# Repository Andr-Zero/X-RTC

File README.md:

# X-RTC
A supplemental Real Time Clock for the Original Xbox 

The Original Xbox does not keep time when unplugged for an extended period of time. While some homebew apps have NTP functionality built in, not everyone plugs the console into their home network every time they play. 

Designed so the battery is only used when AC power is removed from the console. A CR2032 in theory should last 6-10 years when constantly being used. 
Should work with any modchip and TSOPed consoles. Have not tested with BFM BIOSes. 

SDA\SDL from the console are also brought to a set of solder pads for ease of installation of any other mod that may require them. 

# Board Specifications
0.8mm thick, castellated holes on all sides.

# 1.0-1.4 Installation
On the bottom of the Xbox motherboard. If you have a pinheader already installed, remove excessive solder from the pins outlined in purple and any that would interfere with the installation of the X-RTC QSB. Install the QSB onto the LPC port as shown above, make sure the QSB is sitting flush against the board. While keeping the QSB aligned, solder the QSB to the LPC port and the ground point outlined in black. Run a short wire from the console's 3.3v standby outlined in red to the 3v3 StdBy pad on the QSB. Lastly wire a 3v battery to the Positive and Negative solder pads on the QSB.

# 1.6 Installation
On the bottom of the Xbox motherboard. Remove any existing LPC rebuild QSB or wires that maybe installed. If a pinheader is already installed, remove solder from the bottom of the pinheader. No need to remove the pinheader, just enough for the X-RTC QSB can sit flush against the board. Solder the various LAD points first, then the ground connections around the QSB, solder the QSB to the LPC port and pinheader last. Make sure the solder is connecting to the QSB, pinheader, and the main board. All the edge points on the QSB need to contact the board. Since the 1.6 consoles have it’s standby voltage on the LPC, no need to run a wire like the early revisions. Last step is wiring a 3v battery to the Positive and Negative solder pads on the QSB. Your install should look like the 1.6 install at the top of this README

# BOM

| Part | Description | Digikey Link |
| --- | --- | --- |
| `0.1 uF` | Generic 0.1uF Ceramic Cap | https://www.digikey.com/short/408q3vwn |
| `DS3231MZ` | I2C Real Time Clock | https://www.digikey.com/short/m05dd78z |
| `XC6206P332MR` | 3.3v Regulator for 1.6 ONLY | https://www.digikey.com/short/bqdqftzn |

# Software
Cerbios 2.4.0 or higher is required to use X-RTC. 

> ; Enables Automatic Time Sync With Optional RTC Hardware Connected to SMBus
> 
> RtcEnable = True

Using a Chip that can use PrometheOS:
Version 1.4.0 or higher is able to set the time, enable RTC in PrometheOS Settings. (Rebooting recommended) 

TSOP or Other:
Download the X-RTC.xbe into your Apps folder, within you can set the time. 

Once the time is set and Cerbios is configured. The time on the console will set automatically on boot.

# License, Credits, & Thanks
The hardware and it's related files is licensed under CERN-OHL-S v2 or later version.
See License.txt, cern_ohl_s_v2.txt, and cern_ohl_s_v2_user_guide.txt for details.

1.6 LPC rebuild portion by Kekule. -> https://github.com/Kekule-OXC/OXC_LPCorrectr

Team Resurgent for the idea, PrometheOS, and the XBE.

Cerbios team for including functionality into their BIOS.

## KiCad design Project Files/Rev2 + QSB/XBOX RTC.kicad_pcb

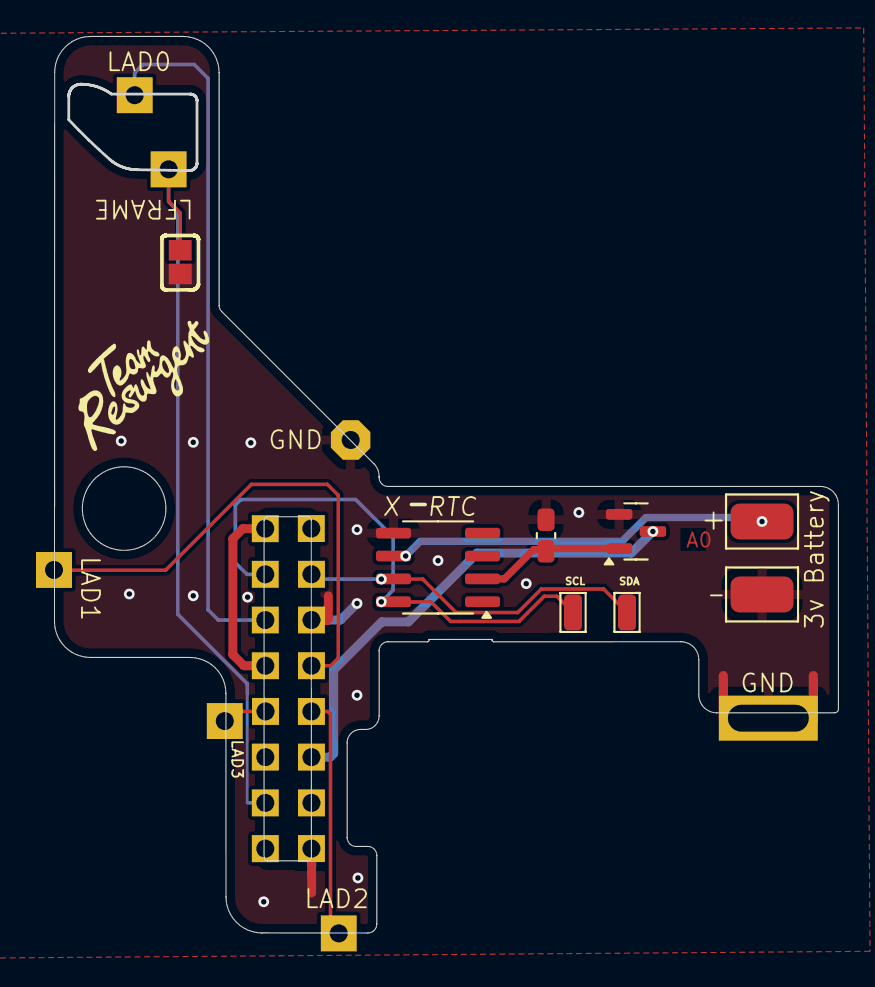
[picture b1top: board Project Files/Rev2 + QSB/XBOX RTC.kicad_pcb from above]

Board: 2 copper layers, 43.4 x 49.7 mm, 7 parts (0 on the bottom side), 5 nets.

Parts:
C1: 0.1uF; C_0603_1608Metric
TP1: SCL; TestPoint_Pad_1.0x2.0mm
TP2: SDA; TestPoint_Pad_1.0x2.0mm
TP3: TestPoint; TestPoint_THTPad_2.5x2.5mm_Drill1.2mm
TP5: Batt +; TestPoint_Pad_1.0x2.0mm
TP6: Batt -; TestPoint_Pad_1.0x2.0mm
U1: DS3231MZ; SOIC-8_3.9x4.9mm_P1.27mm

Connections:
GND: C1.1, TP3.1, TP6.1, U1.5 (GND)
unnamed: TP1.1, U1.8 (SCL)
unnamed: TP2.1, U1.7 (SDA)
unnamed: TP5.1, U1.6 (VBAT)
unnamed: C1.2, U1.2 (VCC)

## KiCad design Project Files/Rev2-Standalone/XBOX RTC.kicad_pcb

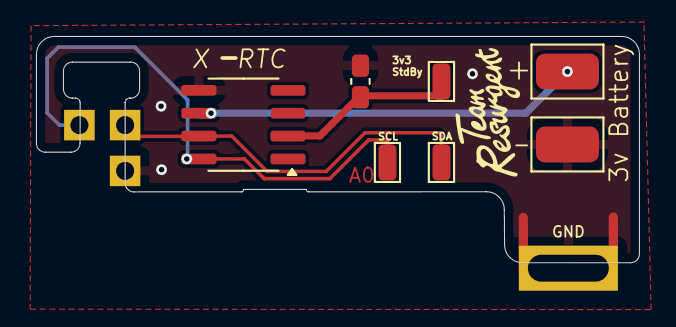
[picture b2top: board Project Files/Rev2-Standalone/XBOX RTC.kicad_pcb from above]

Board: 2 copper layers, 33.5 x 12.6 mm, 9 parts (0 on the bottom side), 5 nets.

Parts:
C1: 0.1uF; C_0603_1608Metric
J3: Xbox LPC; PinSocket_2x08_P2.54mm_Vertical
TP1: SCL; TestPoint_Pad_1.0x2.0mm
TP2: SDA; TestPoint_Pad_1.0x2.0mm
TP3: TestPoint; TestPoint_THTPad_2.5x2.5mm_Drill1.2mm
TP4: 3v3 StdBy; TestPoint_Pad_1.0x2.0mm
TP5: Batt +; TestPoint_Pad_1.0x2.0mm
TP6: Batt -; TestPoint_Pad_1.0x2.0mm
U1: DS3231MZ; SOIC-8_3.9x4.9mm_P1.27mm

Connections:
GND: C1.1, J3.12, TP3.1, TP6.1, U1.5 (GND)
unnamed: J3.13, TP1.1, U1.8 (SCL)
unnamed: J3.14, TP2.1, U1.7 (SDA)
unnamed: TP5.1, U1.6 (VBAT)
unnamed: C1.2, TP4.1, U1.2 (VCC)

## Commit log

2024-07-31 Added App to set the time on the X-RTC board.
2024-08-05 Add files via upload
    Rerouted some traces to allow for better continuous ground planes, Increased the LPC traces to 0.2mm per some various feedback, removed mismatched silkscreens from ground points, added license on bac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
2024-08-05 Add files via upload
    Initial upload of KiCAD files.
2024-08-05 Add files via upload
    License Files uploaded
2024-08-05 Update README.md
    clarification on what license used.
2024-08-05 Add files via upload
    Did not mean to removed the older gerber files...
2024-09-27 Update README.md
    Updating that PrometheOS can also be used to set time on the RTC

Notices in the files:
Project Files/Rev2 + QSB/XBOX RTC.kicad_pcb:
Copyright Andr0 2024, andr0@ogxstore.com
This source describes Open Hardware and is licensed under the
CERN-OHL-S v2 or any later version.
As per CERN-OHL-S v2 section 4, should You produce hardware based on this
